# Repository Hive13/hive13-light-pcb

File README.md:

# hive13-light-pcb
The KiCad files for the lounge light controllers

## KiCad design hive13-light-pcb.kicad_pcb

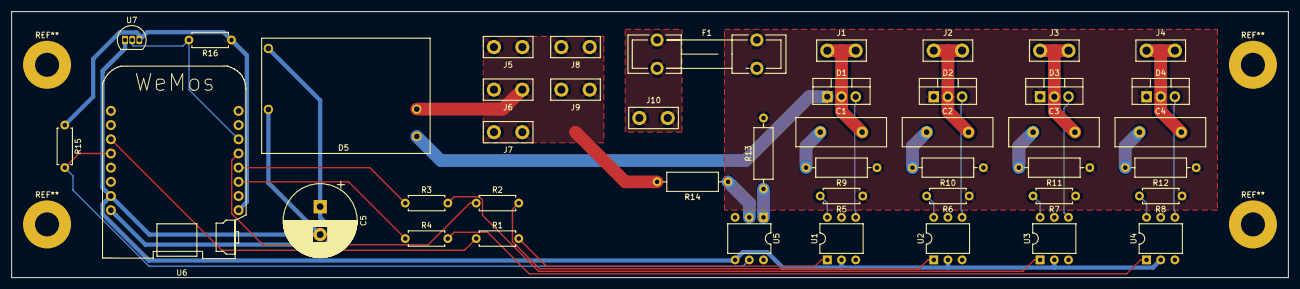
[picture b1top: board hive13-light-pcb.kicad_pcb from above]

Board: 2 copper layers, 228.6 x 47.6 mm, 44 parts (0 on the bottom side), 34 nets.

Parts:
C1, C2, C3, C4: .01MFD; C_Disc_D16.0mm_W5.0mm_P7.50mm
C5: 100MFD; CP_Radial_D13.0mm_P5.00mm
D1, D2, D3, D4: Q_TRIAC_A1A2G; TO-220-3_Vertical
D5: D_Bridge_+-AA; 5V-AC-Module
F1: Fuse; Fuseholder5x20_7
J1, J2, J3, J4, J5, J6, J7, J8, J9, J10: Conn_01x01_Male; 250 Tab
R1, R2, R3, R4: 390Ω; R_Axial_DIN0207_L6.3mm_D2.5mm_P7.62mm_Horizontal
R5, R6, R7, R8: 220Ω; R_Axial_DIN0207_L6.3mm_D2.5mm_P7.62mm_Horizontal
R9, R10, R11, R12: 39Ω; R_Axial_DIN0309_L9.0mm_D3.2mm_P12.70mm_Horizontal
R13, R14: 15kΩ; R_Axial_DIN0309_L9.0mm_D3.2mm_P12.70mm_Horizontal
R15, R16: 4.7kΩ; R_Axial_DIN0207_L6.3mm_D2.5mm_P7.62mm_Horizontal
U1, U2, U3, U4: MOC3011M; DIP-6_W7.62mm
U5: 4N25; DIP-6_W7.62mm
U6: WeMos_mini; D1_mini_board
U7: DS18B20; TO-92L_Inline

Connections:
+3V3: R15.1, R16.1, U6.16, U7.3
/AC: F1.1, J10.1
/FUSED_AC: D1.1, D2.1, D3.1, D4.1, D5.3, F1.2, R5.1, R6.1, R7.1, R8.1, R9.1, R10.1, R11.1, R12.1, R13.2
/GATE_1: D1.3, U1.4
/GATE_2: D2.3, U2.4
/GATE_3: D3.3, U3.4
/GATE_4: D4.3, U4.4
/NEUTRAL: D5.4, J5.1, J6.1, J7.1, J8.1, J9.1, R14.2
/OGATE_1: R5.2, U1.6
/OGATE_2: R6.2, U2.6
/OGATE_3: R7.2, U3.6
/OGATE_4: R8.2, U4.6
/ONE_WIRE: R16.2, U6.11, U7.2
/OUT_1: C1.2, D1.2, J1.1
/OUT_2: C2.2, D2.2, J2.1
/OUT_3: C3.2, D3.2, J3.1
/OUT_4: C4.2, D4.2, J4.1
/SNUB_1: C1.1, R9.2
/SNUB_2: C2.1, R10.2
/SNUB_3: C3.1, R11.2
/SNUB_4: C4.1, R12.2
/TRIAC_1: R1.1, U6.6
/TRIAC_2: R2.1, U6.12
/TRIAC_3: R3.1, U6.13
/TRIAC_4: R4.1, U6.14
/ZCD: R15.2, U5.5, U6.5
GND: C5.2, D5.2, U1.2, U2.2, U3.2, U4.2, U5.4, U6.2, U7.1
unnamed: R1.2, U1.1
unnamed: R2.2, U2.1
unnamed: R3.2, U3.1
unnamed: R4.2, U4.1
unnamed: R13.1, U5.1
unnamed: R14.1, U5.2
VCC: C5.1, D5.1, U6.1

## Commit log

2018-12-15 First check-in of the circuit.
2018-12-19 Work on the circuit board.
2018-12-19 First drawing of the PCB.
2018-12-24 Select masks, too.

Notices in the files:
hive13-light-pcb.kicad_pcb:
(c) 2018 Greg J Arnold
